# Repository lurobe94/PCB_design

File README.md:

# PCB_design
Repo containing the main designs of the RFID attendance system.

This design utilizes another library for the inclusion of the NodeMCU (schematic, footprint...), shared by J.Dunmire in https://github.com/jdunmire/kicad-ESP8266

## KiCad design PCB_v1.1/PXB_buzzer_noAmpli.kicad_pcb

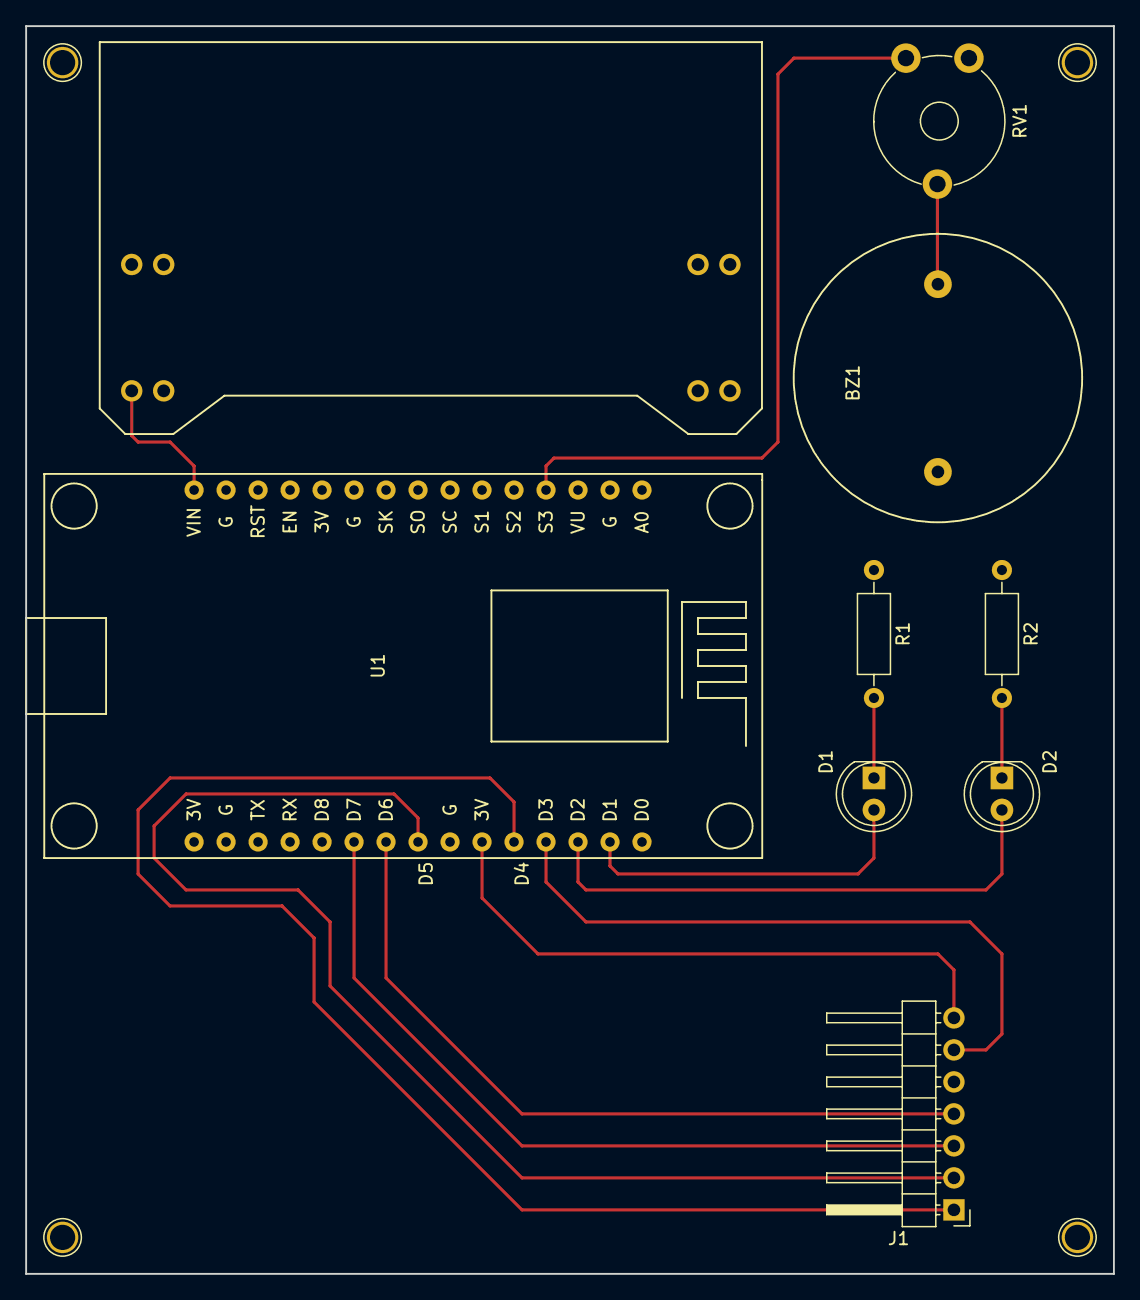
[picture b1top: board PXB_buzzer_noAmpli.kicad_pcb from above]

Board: 2 copper layers, 86.4 x 99.1 mm, 9 parts (0 on the bottom side), 14 nets.

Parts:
BZ1: Buzzer; BUZZER_22mm
D1, D2: LED; LED_D5.0mm
J1: FeAn1x7; Pin_Header_Angled_1x07_Pitch2.54mm
R1, R2: 270Ω; R_Axial_DIN0207_L6.3mm_D2.5mm_P10.16mm_Horizontal
RV1: 10KΩ; Potentiometer_Trimmer_Piher_PT-10v10_Horizontal_Px10.0mm_Py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
U1: NodeMCU_1.0; NodeMCU1.0(12-E)
Y1: YWRobot; YWRobot2

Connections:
/3.3V->7(VCC): J1.7, U1.25
/D1->1(SDA/NSS): J1.1, U1.26
/D3->6(RST): J1.6, U1.27
/D5>2(SCK): J1.2, U1.23
/D6->4(MISO): J1.4, U1.22
/D7->3(MOSI): J1.3, U1.21
/GND->5(GND): BZ1.2, J1.5, R1.1, R2.1, RV1.3, U1.2, U1.10, U1.14, U1.17, U1.24, Y1.3, Y1.5, Y1.6, Y1.7
unnamed: BZ1.1, RV1.2
unnamed: D1.1, R1.2
unnamed: D1.2, U1.29
unnamed: D2.1, R2.2
unnamed: D2.2, U1.28
unnamed: RV1.1, U1.4
unnamed: U1.15, Y1.4

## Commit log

2018-01-30 PCB Design v.1
2018-02-02 PCB with mounting holes
